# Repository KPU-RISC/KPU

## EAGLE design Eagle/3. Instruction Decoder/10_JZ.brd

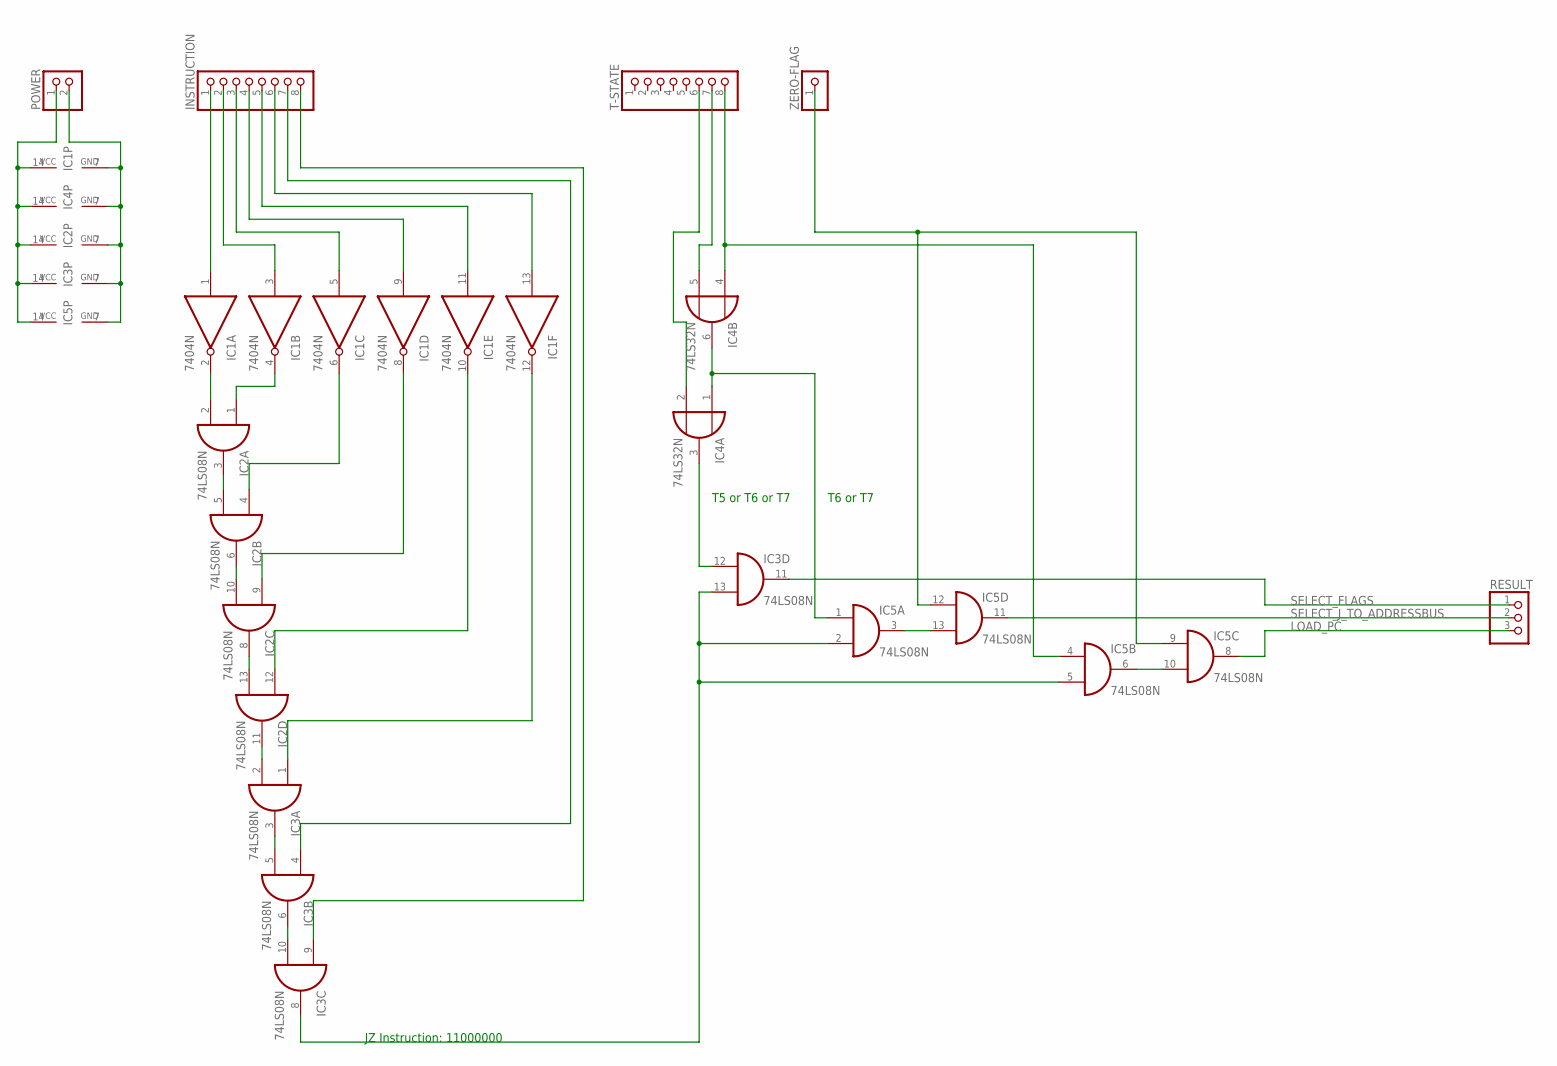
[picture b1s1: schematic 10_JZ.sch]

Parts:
IC1: 7404N; DIL14
IC2, IC3, IC5: 74LS08N; DIL14
IC4: 74LS32N; DIL14
INSTRUCTION: PINHD-1X8; 1X08
POWER: PINHD-1X2; 1X02
RESULT: PINHD-1X3; 1X03
T-STATE: PINHD-1X8; 1X08
ZERO-FLAG: PINHD-1X1; 1X01

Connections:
GND: IC1.7 (GND), IC2.7 (GND), IC3.7 (GND), IC4.7 (GND), IC5.7 (GND), POWER.2
LOAD_PC: IC5.8 (O), RESULT.3
unnamed: IC1.1 (I), INSTRUCTION.1
unnamed: IC1.3 (I), INSTRUCTION.2
unnamed: IC1.5 (I), INSTRUCTION.3
unnamed: IC1.9 (I), INSTRUCTION.4
unnamed: IC1.11 (I), INSTRUCTION.5
unnamed: IC1.13 (I), INSTRUCTION.6
unnamed: IC3.4 (I0), INSTRUCTION.7
unnamed: IC3.9 (I0), INSTRUCTION.8
unnamed: IC1.2 (O), IC2.2 (I1)
unnamed: IC1.4 (O), IC2.1 (I0)
unnamed: IC2.3 (O), IC2.5 (I1)
unnamed: IC1.6 (O), IC2.4 (I0)
unnamed: IC2.6 (O), IC2.10 (I1)
unnamed: IC1.8 (O), IC2.9 (I0)
unnamed: IC2.8 (O), IC2.13 (I1)
unnamed: IC1.10 (O), IC2.12 (I0)
unnamed: IC2.11 (O), IC3.2 (I1)
unnamed: IC3.3 (O), IC3.5 (I1)
unnamed: IC1.12 (O), IC3.1 (I0)
unnamed: IC3.6 (O), IC3.10 (I1)
unnamed: IC5.6 (O), IC5.10 (I1)
unnamed: IC3.8 (O), IC3.13 (I1), IC5.2 (I1), IC5.5 (I1)
unnamed: IC4.4 (I0), IC5.4 (I0), T-STATE.8
unnamed: IC4.5 (I1), T-STATE.7
unnamed: IC4.1 (I0), IC4.6 (O), IC5.1 (I0)
unnamed: IC4.2 (I1), T-STATE.6
unnamed: IC3.12 (I0), IC4.3 (O)
unnamed: IC5.9 (I0), IC5.12 (I0), ZERO-FLAG.1
unnamed: IC5.3 (O), IC5.13 (I1)
SELECT_FLAGS: IC3.11 (O), RESULT.1
SELECT_J_TO_ADDRESSBUS: IC5.11 (O), RESULT.2
VCC: IC1.14 (VCC), IC2.14 (VCC), IC3.14 (VCC), IC4.14 (VCC), IC5.14 (VCC), POWER.1

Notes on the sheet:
JZ Instruction: 11000000
T5 or T6 or T7
T6 or T7

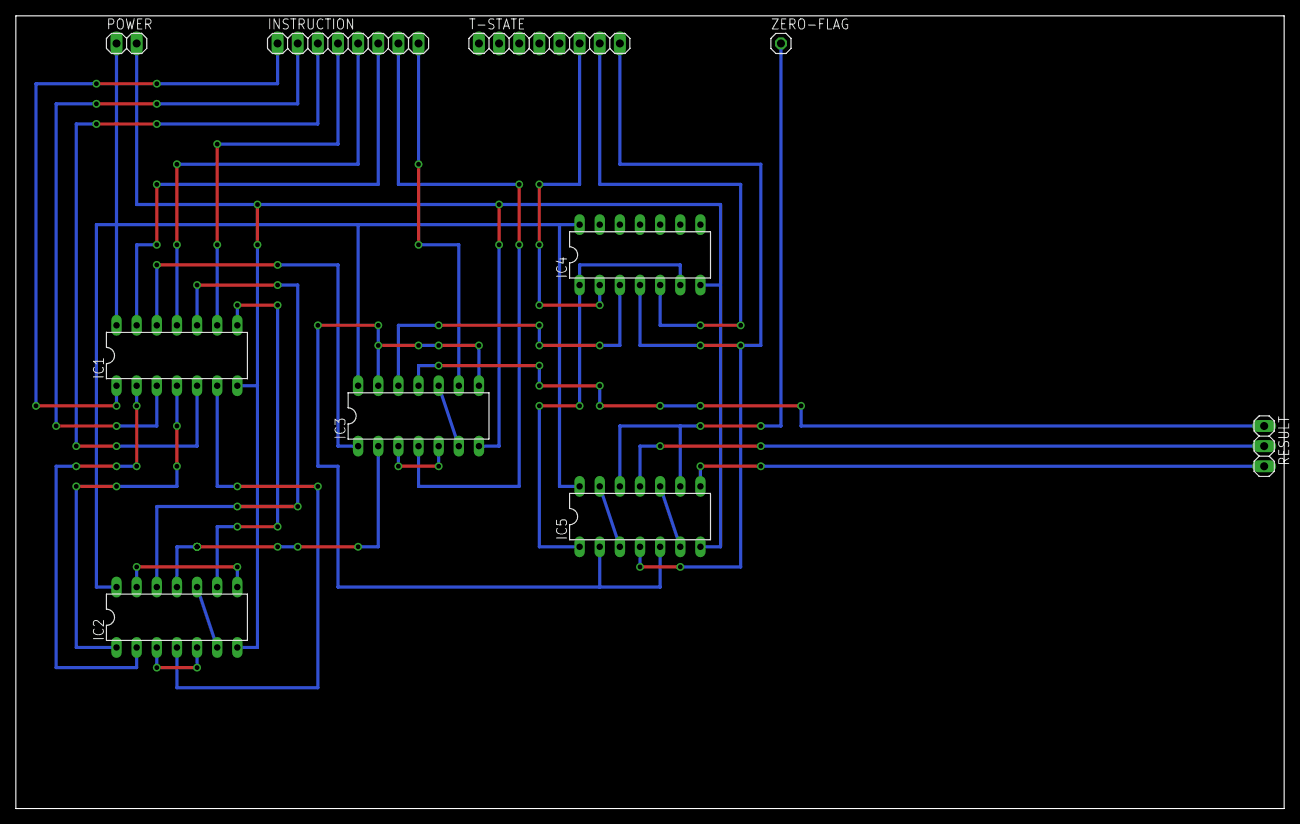
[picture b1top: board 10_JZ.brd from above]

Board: 2 copper layers, 160.0 x 100.0 mm, 10 parts (0 on the bottom side), 34 nets.

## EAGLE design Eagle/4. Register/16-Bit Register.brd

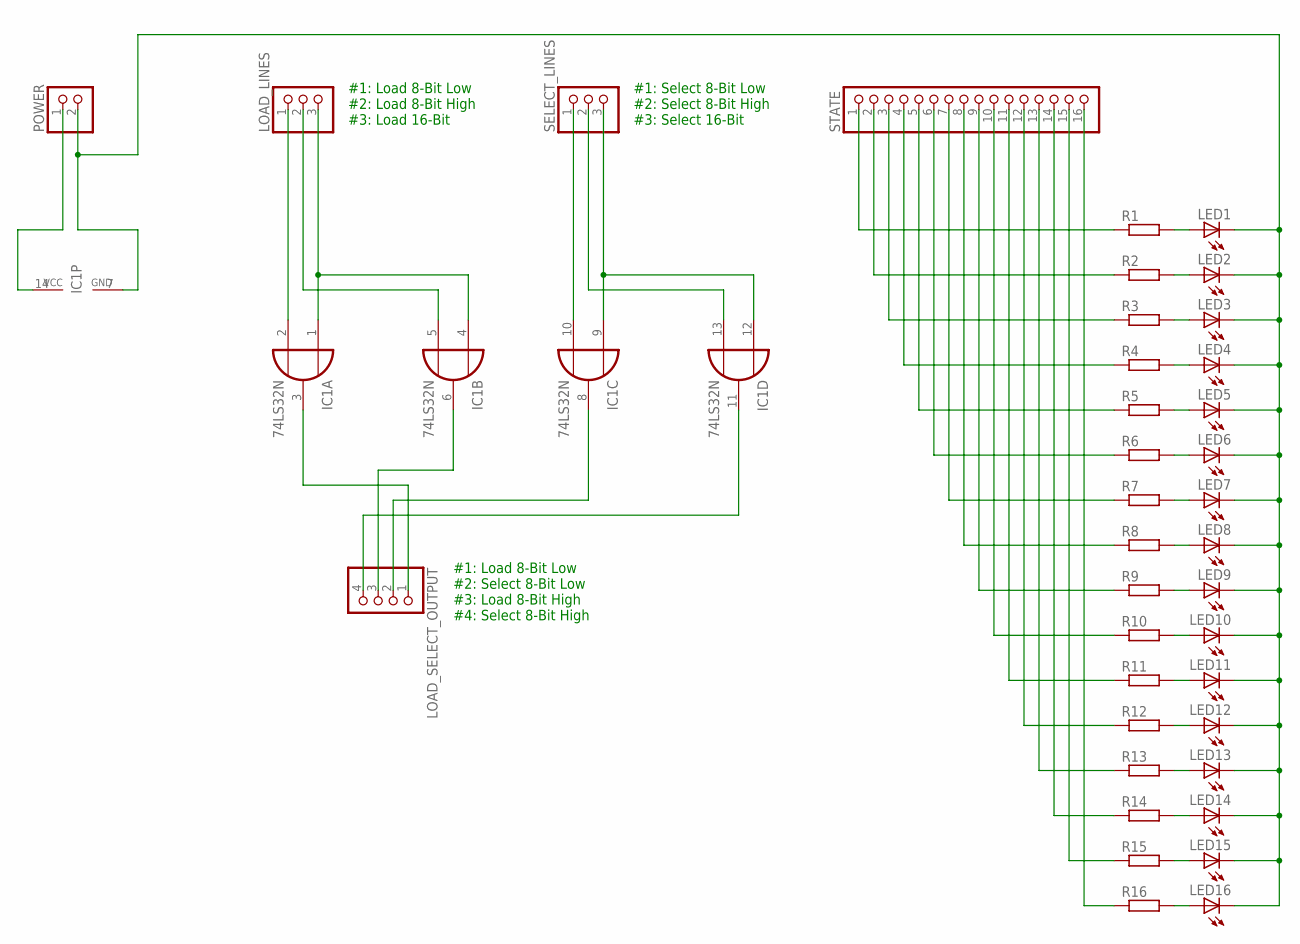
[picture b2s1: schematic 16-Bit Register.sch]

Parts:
IC1: 74LS32N; DIL14
LED1, LED2, LED3, LED4, LED5, LED6, LED7, LED8, LED9, LED10, LED11, LED12, LED13, LED14, LED15, LED16: LED3MM
LOAD_LINES: PINHD-1X3; 1X03
LOAD_SELECT_OUTPUT: PINHD-1X4; 1X04
POWER: PINHD-1X2; 1X02
R1, R2, R3, R4, R5, R6, R7, R8, R9, R10, R11, R12, R13, R14, R15, R16: R-EU_0207/7; 0207/7
SELECT_LINES: PINHD-1X3; 1X03
STATE: PINHD-1X16; 1X16

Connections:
GND: IC1.7 (GND), LED1.K (C), LED2.K (C), LED3.K (C), LED4.K (C), LED5.K (C), LED6.K (C), LED7.K (C), LED8.K (C), LED9.K (C), LED10.K (C), LED11.K (C), LED12.K (C), LED13.K (C), LED14.K (C), LED15.K (C), LED16.K (C), POWER.2
unnamed: IC1.2 (I1), LOAD_LINES.1
unnamed: IC1.1 (I0), IC1.4 (I0), LOAD_LINES.3
unnamed: IC1.5 (I1), LOAD_LINES.2
unnamed: IC1.10 (I1), SELECT_LINES.1
unnamed: IC1.9 (I0), IC1.12 (I0), SELECT_LINES.3
unnamed: IC1.13 (I1), SELECT_LINES.2
unnamed: IC1.3 (O), LOAD_SELECT_OUTPUT.1
unnamed: IC1.6 (O), LOAD_SELECT_OUTPUT.3
unnamed: IC1.8 (O), LOAD_SELECT_OUTPUT.2
unnamed: IC1.11 (O), LOAD_SELECT_OUTPUT.4
unnamed: R1.1, STATE.1
unnamed: R2.1, STATE.2
unnamed: R3.1, STATE.3
unnamed: R4.1, STATE.4
unnamed: R5.1, STATE.5
unnamed: R6.1, STATE.6
unnamed: R7.1, STATE.7
unnamed: R8.1, STATE.8
unnamed: R9.1, STATE.9
unnamed: R10.1, STATE.10
unnamed: R11.1, STATE.11
unnamed: R12.1, STATE.12
unnamed: R13.1, STATE.13
unnamed: R14.1, STATE.14
unnamed: R15.1, STATE.15
unnamed: R16.1, STATE.16
unnamed: LED16.A, R16.2
unnamed: LED15.A, R15.2
unnamed: LED14.A, R14.2
unnamed: LED13.A, R13.2
unnamed: LED12.A, R12.2
unnamed: LED11.A, R11.2
unnamed: LED10.A, R10.2
unnamed: LED9.A, R9.2
unnamed: LED8.A, R8.2
unnamed: LED7.A, R7.2
unnamed: LED6.A, R6.2
unnamed: LED5.A, R5.2
unnamed: LED4.A, R4.2
unnamed: LED3.A, R3.2
unnamed: LED2.A, R2.2
unnamed: LED1.A, R1.2
VCC: IC1.14 (VCC), POWER.1

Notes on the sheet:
#1: Load 8-Bit Low #2: Load 8-Bit High #3: Load 16-Bit
#1: Select 8-Bit Low #2: Select 8-Bit High #3: Select 16-Bit
#1: Load 8-Bit Low #2: Select 8-Bit Low #3: Load 8-Bit High #4: Select 8-Bit High

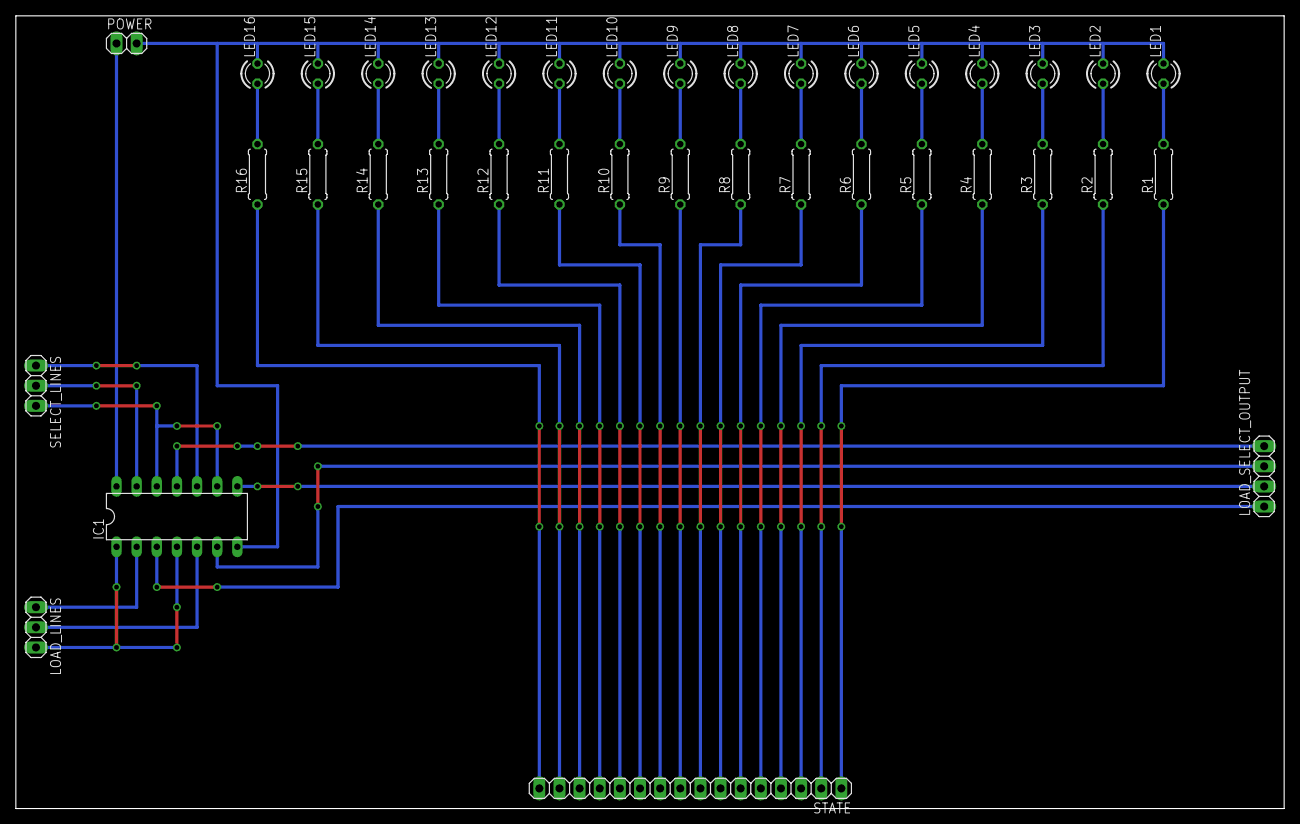
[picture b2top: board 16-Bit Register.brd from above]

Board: 2 copper layers, 160.0 x 100.0 mm, 38 parts (0 on the bottom side), 44 nets.

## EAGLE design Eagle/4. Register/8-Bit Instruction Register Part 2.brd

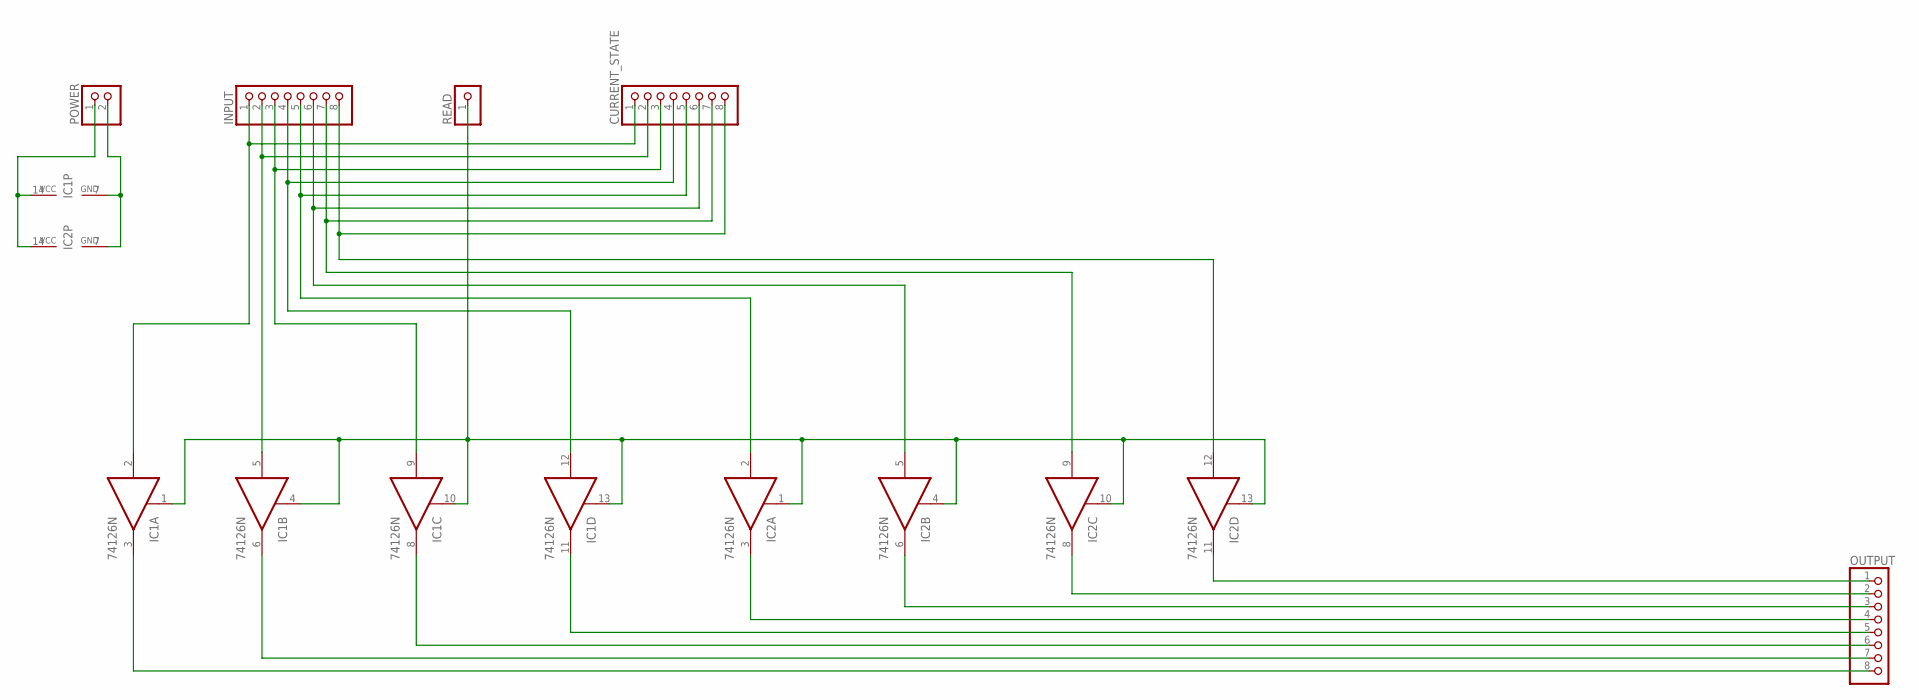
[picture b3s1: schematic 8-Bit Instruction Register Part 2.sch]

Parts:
CURRENT_STATE: PINHD-1X8; 1X08
IC1, IC2: 74126N; DIL14
INPUT: PINHD-1X8; 1X08
OUTPUT: PINHD-1X8; 1X08
POWER: PINHD-1X2; 1X02
READ: PINHD-1X1; 1X01

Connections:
GND: IC1.7 (GND), IC2.7 (GND), POWER.2
unnamed: CURRENT_STATE.1, IC1.2 (I), INPUT.1
unnamed: CURRENT_STATE.2, IC1.5 (I), INPUT.2
unnamed: CURRENT_STATE.3, IC1.9 (I), INPUT.3
unnamed: CURRENT_STATE.4, IC1.12 (I), INPUT.4
unnamed: CURRENT_STATE.5, IC2.2 (I), INPUT.5
unnamed: CURRENT_STATE.6, IC2.5 (I), INPUT.6
unnamed: CURRENT_STATE.7, IC2.9 (I), INPUT.7
unnamed: CURRENT_STATE.8, IC2.12 (I), INPUT.8
unnamed: IC1.1 (OE), IC1.4 (OE), IC1.10 (OE), IC1.13 (OE), IC2.1 (OE), IC2.4 (OE), IC2.10 (OE), IC2.13 (OE), READ.1
unnamed: IC1.3 (O), OUTPUT.8
unnamed: IC1.6 (O), OUTPUT.7
unnamed: IC1.8 (O), OUTPUT.6
unnamed: IC1.11 (O), OUTPUT.5
unnamed: IC2.3 (O), OUTPUT.4
unnamed: IC2.6 (O), OUTPUT.3
unnamed: IC2.8 (O), OUTPUT.2
unnamed: IC2.11 (O), OUTPUT.1
VCC: IC1.14 (VCC), IC2.14 (VCC), POWER.1

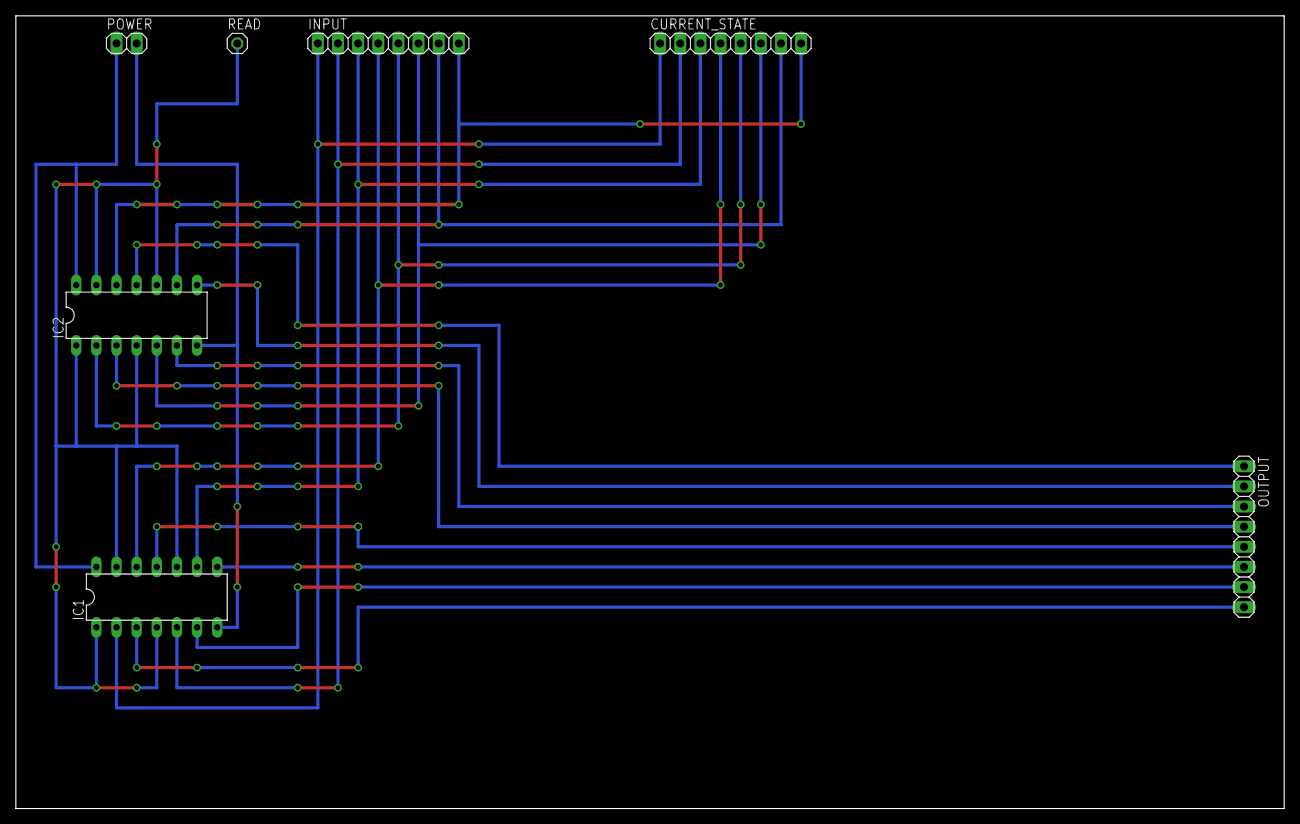
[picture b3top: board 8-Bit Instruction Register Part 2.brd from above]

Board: 2 copper layers, 160.0 x 100.0 mm, 7 parts (0 on the bottom side), 19 nets.

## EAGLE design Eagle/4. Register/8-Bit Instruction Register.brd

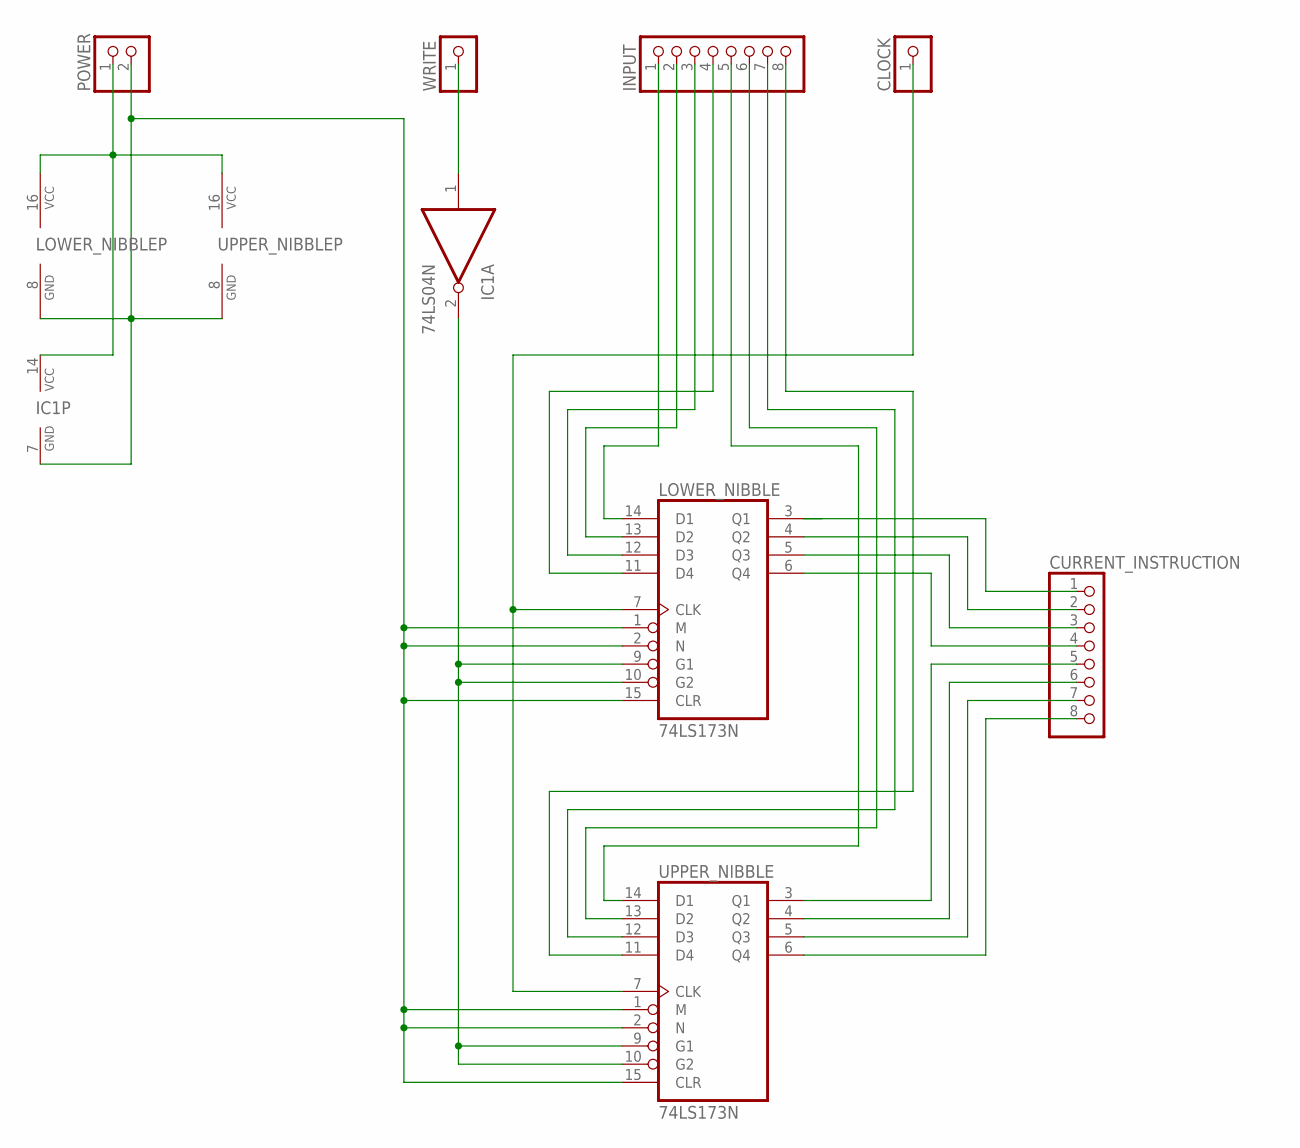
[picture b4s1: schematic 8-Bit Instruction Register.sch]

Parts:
CLOCK: PINHD-1X1; 1X01
CURRENT_INSTRUCTION: PINHD-1X8; 1X08
IC1: 74LS04N; DIL14
INPUT: PINHD-1X8; 1X08
LOWER_NIBBLE: 74LS173N; DIL16
POWER: PINHD-1X2; 1X02
UPPER_NIBBLE: 74LS173N; DIL16
WRITE: PINHD-1X1; 1X01

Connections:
GND: IC1.7 (GND), LOWER_NIBBLE.1 (M), LOWER_NIBBLE.2 (N), LOWER_NIBBLE.8 (GND), LOWER_NIBBLE.15 (CLR), POWER.2, UPPER_NIBBLE.1 (M), UPPER_NIBBLE.2 (N), UPPER_NIBBLE.8 (GND), UPPER_NIBBLE.15 (CLR)
unnamed: IC1.1 (I), WRITE.1
unnamed: CURRENT_INSTRUCTION.4, LOWER_NIBBLE.6 (Q4)
unnamed: IC1.2 (O), LOWER_NIBBLE.9 (G1), LOWER_NIBBLE.10 (G2), UPPER_NIBBLE.9 (G1), UPPER_NIBBLE.10 (G2)
unnamed: CLOCK.1, LOWER_NIBBLE.7 (CLK), UPPER_NIBBLE.7 (CLK)
unnamed: INPUT.1, LOWER_NIBBLE.14 (D1)
unnamed: INPUT.2, LOWER_NIBBLE.13 (D2)
unnamed: INPUT.3, LOWER_NIBBLE.12 (D3)
unnamed: INPUT.4, LOWER_NIBBLE.11 (D4)
unnamed: INPUT.6, UPPER_NIBBLE.13 (D2)
unnamed: INPUT.5, UPPER_NIBBLE.14 (D1)
unnamed: INPUT.7, UPPER_NIBBLE.12 (D3)
unnamed: INPUT.8, UPPER_NIBBLE.11 (D4)
unnamed: CURRENT_INSTRUCTION.8, UPPER_NIBBLE.6 (Q4)
unnamed: CURRENT_INSTRUCTION.1, LOWER_NIBBLE.3 (Q1)
unnamed: CURRENT_INSTRUCTION.2, LOWER_NIBBLE.4 (Q2)
unnamed: CURRENT_INSTRUCTION.3, LOWER_NIBBLE.5 (Q3)
unnamed: CURRENT_INSTRUCTION.5, UPPER_NIBBLE.3 (Q1)
unnamed: CURRENT_INSTRUCTION.6, UPPER_NIBBLE.4 (Q2)
unnamed: CURRENT_INSTRUCTION.7, UPPER_NIBBLE.5 (Q3)
VCC: IC1.14 (VCC), LOWER_NIBBLE.16 (VCC), POWER.1, UPPER_NIBBLE.16 (VCC)

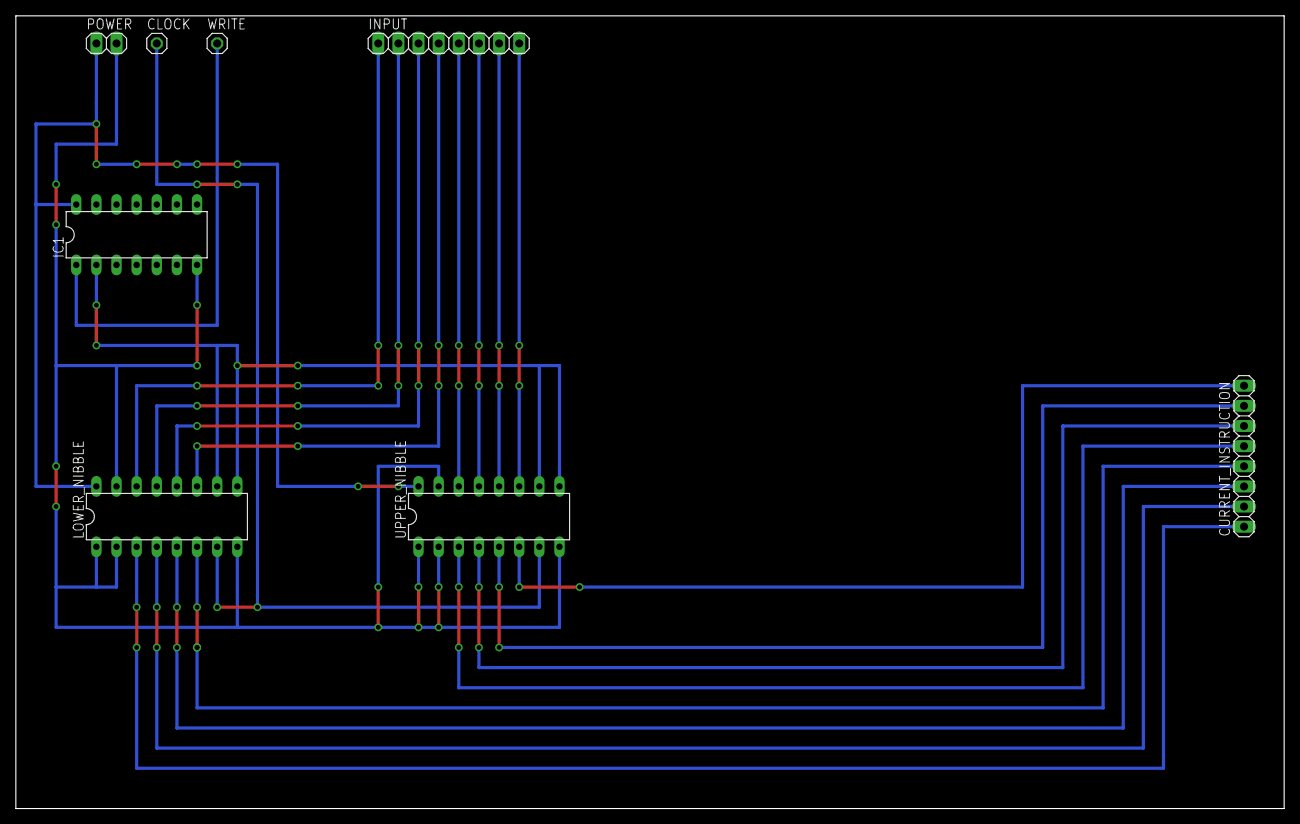
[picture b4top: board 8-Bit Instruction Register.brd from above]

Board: 2 copper layers, 160.0 x 100.0 mm, 8 parts (0 on the bottom side), 21 nets.
